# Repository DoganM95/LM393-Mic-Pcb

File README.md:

# LM393-Mic-Pcb
LM393 based microphone module for arduinos. This wil become a part of another bigger project and serves as a copyable module for it. PCB prototype is for testing the circuit and seeing if it catches fire or not.

## Visual Overview
<table>
  <tr>
    <td>
      
    </td>
    <td>
      
    </td>
    <!--
    <td>
      
    </td>
    <td>
      
    </td>
    -->
  </tr>
</table>

## Key Features

- 22.12mm height x 12.7mm width x 1.6mm thickness 
- Adjustable mic sensitivity
- Choosable led colors (short the corresponding jumper)
  - Power Led: JP1:Red, JP2:Green, JP3:Blue,
  - Output Led: JP4:Red, JP5:Green, JP5:Blue

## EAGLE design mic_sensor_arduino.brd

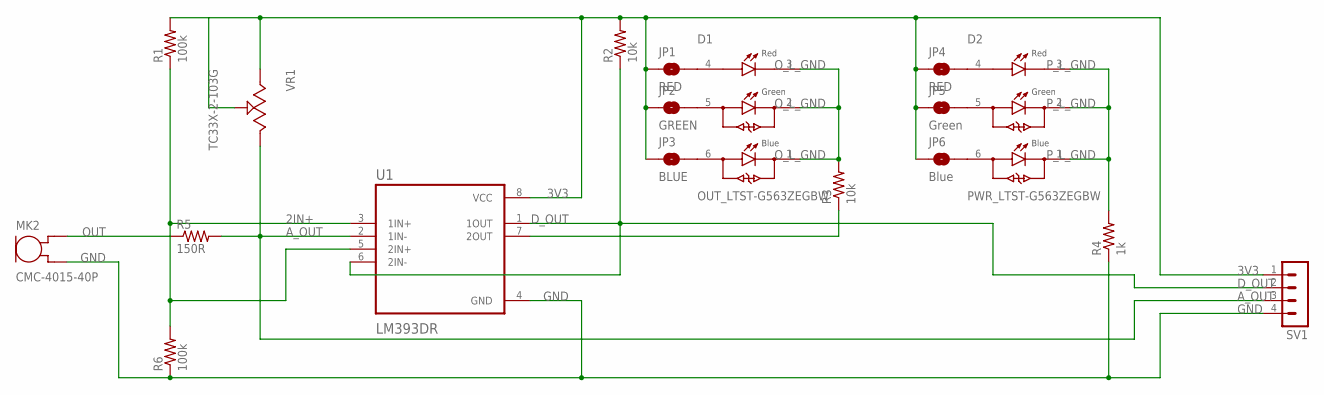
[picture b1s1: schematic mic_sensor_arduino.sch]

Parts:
D1: OUT_LTST-G563ZEGBW; LED_LTST-G563ZEGBW
D2: PWR_LTST-G563ZEGBW; LED_LTST-G563ZEGBW
JP1, JP4: RED; SMT-JUMPER_2_NO_SILK
JP2: GREEN; SMT-JUMPER_2_NO_SILK
JP3: BLUE; SMT-JUMPER_2_NO_SILK
JP5: Green; SMT-JUMPER_2_NO_SILK
JP6: Blue; SMT-JUMPER_2_NO_SILK
MK2: CMC-4015-40P; MIC_CMC-4015-40P
R1, R6: 100k; R0603
R2, R3: 10k; R0603
R4: 1k; R0603
R5: 150R; R0603
SV1: MA04-1
U1: LM393DR; SOIC127P599X175-8N
VR1: TC33X-2-103G; TRIMMER_TC33X-2-103G

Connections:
2IN+: R1.1, R6.2, U1.3 (1IN+), U1.5 (2IN+)
2OUT: R3.1, U1.7 (2OUT)
3V3: JP1.1, JP2.1, JP3.1, JP4.1, JP5.1, JP6.1, R1.2, R2.2, SV1.1, U1.8 (VCC), VR1.1 (CCW), VR1.2 (WIPER)
A_OUT: R5.2, SV1.3, U1.2 (1IN-), VR1.3 (CW)
D_OUT: R2.1, SV1.2, U1.1 (1OUT), U1.6 (2IN-)
GND: MK2.M (GND), R4.1, R6.1, SV1.4, U1.4 (GND)
unnamed: D1.4, JP1.2
unnamed: D1.5, JP2.2
unnamed: D1.6, JP3.2
unnamed: D2.4, JP4.2
unnamed: D2.5, JP5.2
unnamed: D2.6, JP6.2
OUT: MK2.P (OUT), R5.1
O_L_GND: D1.1, D1.2, D1.3, R3.2
P_L_GND: D2.1, D2.2, D2.3, R4.2

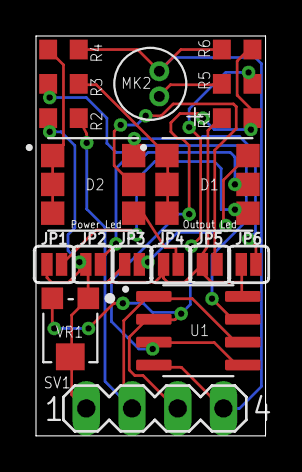
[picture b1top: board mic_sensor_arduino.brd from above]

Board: 2 copper layers, 12.8 x 22.2 mm, 18 parts (0 on the bottom side), 15 nets.

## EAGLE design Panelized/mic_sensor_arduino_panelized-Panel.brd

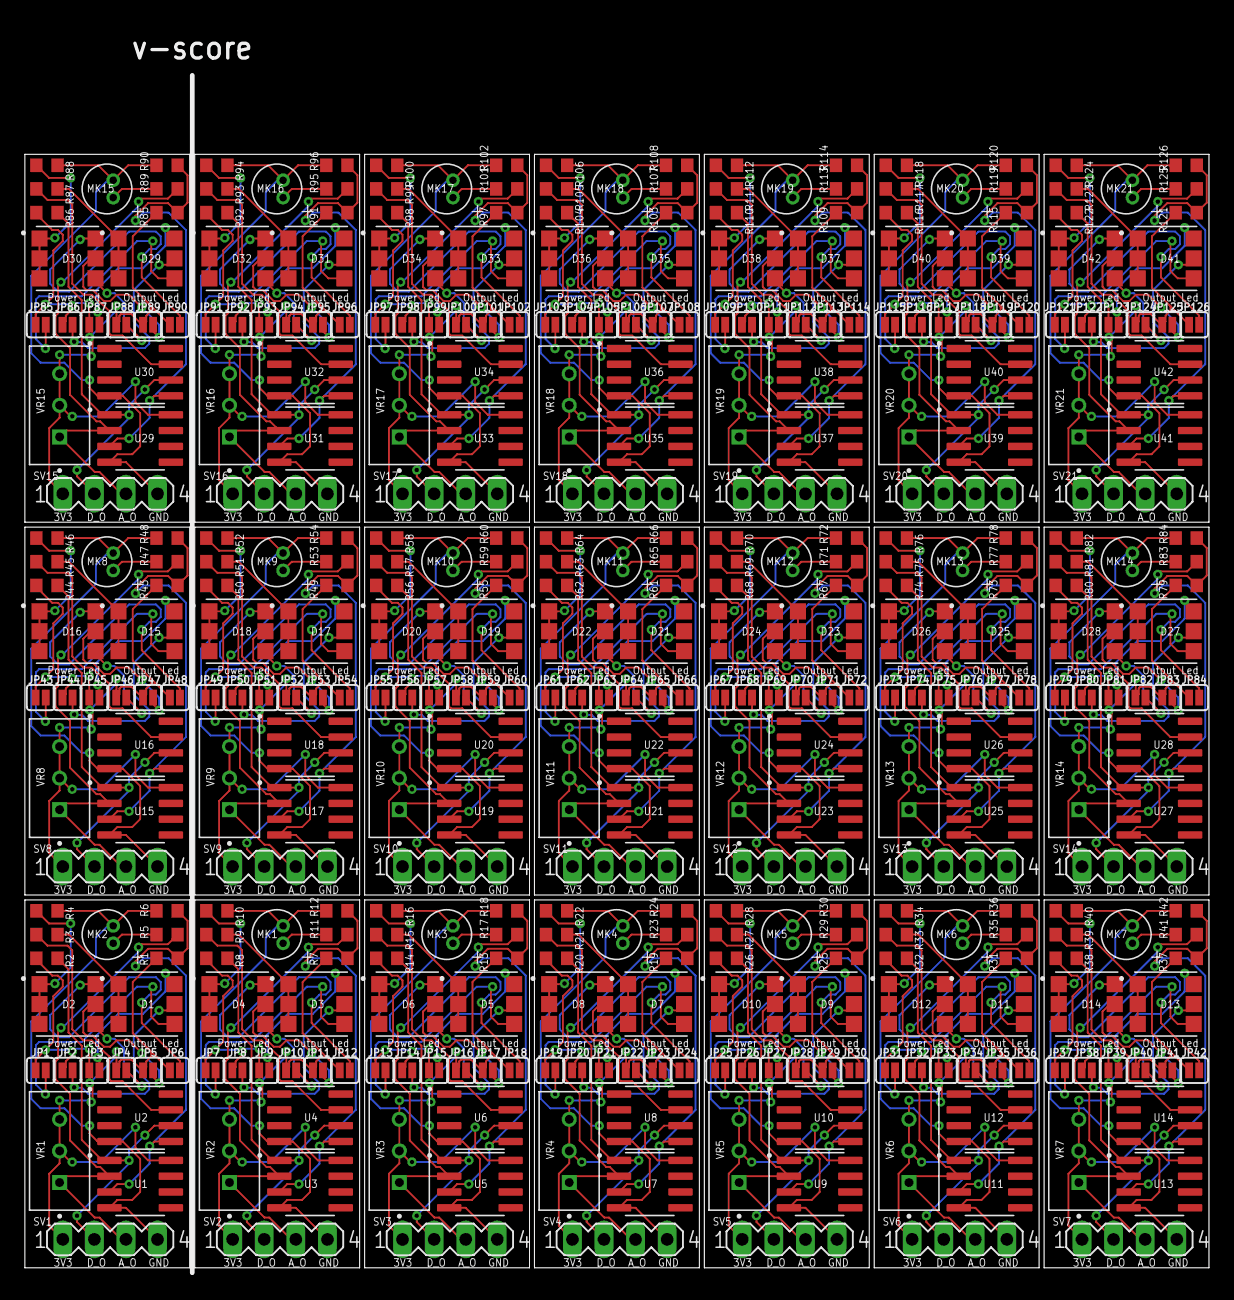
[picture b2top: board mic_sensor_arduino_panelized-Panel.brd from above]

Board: 2 copper layers, 94.8 x 100.2 mm, 399 parts (0 on the bottom side), 315 nets.

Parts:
D1, D3, D5, D7, D9, D11, D13, D15, D17, D19, D21, D23, D25, D27, D29, D31, D33, D35, D37, D39, D41: OUT_LTST-G563ZEGBW; LED_LTST-G563ZEGBW
D2, D4, D6, D8, D10, D12, D14, D16, D18, D20, D22, D24, D26, D28, D30, D32, D34, D36, D38, D40, D42: PWR_LTST-G563ZEGBW; LED_LTST-G563ZEGBW
JP1, JP4, JP7, JP10, JP13, JP16, JP19, JP22, JP25, JP28, JP31, JP34, JP37, JP40, JP43, JP46, JP49, JP52, JP55, JP58, JP61, JP64, JP67, JP70, JP73, JP76, JP79, JP82, JP85, JP88, JP91, JP94, JP97, JP100, JP103, JP106, JP109, JP112, JP115, JP118, JP121, JP124: RED; SMT-JUMPER_2_NO_SILK
JP2, JP8, JP14, JP20, JP26, JP32, JP38, JP44, JP50, JP56, JP62, JP68, JP74, JP80, JP86, JP92, JP98, JP104, JP110, JP116, JP122: GREEN; SMT-JUMPER_2_NO_SILK
JP3, JP9, JP15, JP21, JP27, JP33, JP39, JP45, JP51, JP57, JP63, JP69, JP75, JP81, JP87, JP93, JP99, JP105, JP111, JP117, JP123: BLUE; SMT-JUMPER_2_NO_SILK
JP5, JP11, JP17, JP23, JP29, JP35, JP41, JP47, JP53, JP59, JP65, JP71, JP77, JP83, JP89, JP95, JP101, JP107, JP113, JP119, JP125: Green; SMT-JUMPER_2_NO_SILK
JP6, JP12, JP18, JP24, JP30, JP36, JP42, JP48, JP54, JP60, JP66, JP72, JP78, JP84, JP90, JP96, JP102, JP108, JP114, JP120, JP126: Blue; SMT-JUMPER_2_NO_SILK
MK1, MK2, MK3, MK4, MK5, MK6, MK7, MK8, MK9, MK10, MK11, MK12, MK13, MK14, MK15, MK16, MK17, MK18, MK19, MK20, MK21: CMC-4015-40P; MIC_CMC-4015-40P
R1, R6, R7, R12, R13, R18, R19, R24, R25, R30, R31, R36, R37, R42, R43, R48, R49, R54, R55, R60, R61, R66, R67, R72, R73, R78, R79, R84, R85, R90, R91, R96, R97, R102, R103, R108, R109, R114, R115, R120, R121, R126: 100k; R0603
R2, R3, R8, R9, R14, R15, R20, R21, R26, R27, R32, R33, R38, R39, R44, R45, R50, R51, R56, R57, R62, R63, R68, R69, R74, R75, R80, R81, R86, R87, R92, R93, R98, R99, R104, R105, R110, R111, R116, R117, R122, R123: 10k; R0603
R4, R10, R16, R22, R28, R34, R40, R46, R52, R58, R64, R70, R76, R82, R88, R94, R100, R106, R112, R118, R124: 1k; R0603
R5, R11, R17, R23, R29, R35, R41, R47, R53, R59, R65, R71, R77, R83, R89, R95, R101, R107, R113, R119, R125: 150R; R0603
SV1, SV2, SV3, SV4, SV5, SV6, SV7, SV8, SV9, SV10, SV11, SV12, SV13, SV14, SV15, SV16, SV17, SV18, SV19, SV20, SV21: MA04-1
U1, U2, U3, U4, U5, U6, U7, U8, U9, U10, U11, U12, U13, U14, U15, U16, U17, U18, U19, U20, U21, U22, U23, U24, U25, U26, U27, U28, U29, U30, U31, U32, U33, U34, U35, U36, U37, U38, U39, U40, U41, U42: LM393DR; SOIC127P599X175-8N
VR1, VR2, VR3, VR4, VR5, VR6, VR7, VR8, VR9, VR10, VR11, VR12, VR13, VR14, VR15, VR16, VR17, VR18, VR19, VR20, VR21: 3296W-1-103RLF; TRIM_3296W-1-103RLF

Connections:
2IN+: R1.1, R6.2, U1.3, U2.5
2IN+1: R7.1, R12.2, U3.3, U4.5
2IN+2: R13.1, R18.2, U5.3, U6.5
2IN+3: R19.1, R24.2, U7.3, U8.5
2IN+4: R25.1, R30.2, U9.3, U10.5
2IN+5: R31.1, R36.2, U11.3, U12.5
2IN+6: R37.1, R42.2, U13.3, U14.5
2IN+7: R43.1, R48.2, U15.3, U16.5
2IN+8: R49.1, R54.2, U17.3, U18.5
2IN+9: R55.1, R60.2, U19.3, U20.5
2IN+10: R61.1, R66.2, U21.3, U22.5
2IN+11: R67.1, R72.2, U23.3, U24.5
2IN+12: R73.1, R78.2, U25.3, U26.5
2IN+13: R79.1, R84.2, U27.3, U28.5
2IN+14: R85.1, R90.2, U29.3, U30.5
2IN+15: R91.1, R96.2, U31.3, U32.5
2IN+16: R97.1, R102.2, U33.3, U34.5
2IN+17: R103.1, R108.2, U35.3, U36.5
2IN+18: R109.1, R114.2, U37.3, U38.5
2IN+19: R115.1, R120.2, U39.3, U40.5
2IN+20: R121.1, R126.2, U41.3, U42.5
2OUT: R3.1, U2.7
2OUT1: R9.1, U4.7
2OUT2: R15.1, U6.7
2OUT3: R21.1, U8.7
2OUT4: R27.1, U10.7
2OUT5: R33.1, U12.7
2OUT6: R39.1, U14.7
2OUT7: R45.1, U16.7
2OUT8: R51.1, U18.7
2OUT9: R57.1, U20.7
2OUT10: R63.1, U22.7
2OUT11: R69.1, U24.7
2OUT12: R75.1, U26.7
2OUT13: R81.1, U28.7
2OUT14: R87.1, U30.7
2OUT15: R93.1, U32.7
2OUT16: R99.1, U34.7
2OUT17: R105.1, U36.7
2OUT18: R111.1, U38.7
2OUT19: R117.1, U40.7
2OUT20: R123.1, U42.7
3V1: JP7.1, JP8.1, JP9.1, JP10.1, JP11.1, JP12.1, R7.2, R8.2, SV2.1, U3.8, VR2.2, VR2.3
3V2: JP13.1, JP14.1, JP15.1, JP16.1, JP17.1, JP18.1, R13.2, R14.2, SV3.1, U5.8, VR3.2, VR3.3
3V3: JP1.1, JP2.1, JP3.1, JP4.1, JP5.1, JP6.1, R1.2, R2.2, SV1.1, U1.8, VR1.2, VR1.3
3V4: JP19.1, JP20.1, JP21.1, JP22.1, JP23.1, JP24.1, R19.2, R20.2, SV4.1, U7.8, VR4.2, VR4.3
3V5: JP25.1, JP26.1, JP27.1, JP28.1, JP29.1, JP30.1, R25.2, R26.2, SV5.1, U9.8, VR5.2, VR5.3
3V6: JP31.1, JP32.1, JP33.1, JP34.1, JP35.1, JP36.1, R31.2, R32.2, SV6.1, U11.8, VR6.2, VR6.3
3V7: JP37.1, JP38.1, JP39.1, JP40.1, JP41.1, JP42.1, R37.2, R38.2, SV7.1, U13.8, VR7.2, VR7.3
3V8: JP43.1, JP44.1, JP45.1, JP46.1, JP47.1, JP48.1, R43.2, R44.2, SV8.1, U15.8, VR8.2, VR8.3
3V9: JP49.1, JP50.1, JP51.1, JP52.1, JP53.1, JP54.1, R49.2, R50.2, SV9.1, U17.8, VR9.2, VR9.3
3V10: JP55.1, JP56.1, JP57.1, JP58.1, JP59.1, JP60.1, R55.2, R56.2, SV10.1, U19.8, VR10.2, VR10.3
3V11: JP61.1, JP62.1, JP63.1, JP64.1, JP65.1, JP66.1, R61.2, R62.2, SV11.1, U21.8, VR11.2, VR11.3
3V12: JP67.1, JP68.1, JP69.1, JP70.1, JP71.1, JP72.1, R67.2, R68.2, SV12.1, U23.8, VR12.2, VR12.3
3V13: JP73.1, JP74.1, JP75.1, JP76.1, JP77.1, JP78.1, R73.2, R74.2, SV13.1, U25.8, VR13.2, VR13.3
3V14: JP79.1, JP80.1, JP81.1, JP82.1, JP83.1, JP84.1, R79.2, R80.2, SV14.1, U27.8, VR14.2, VR14.3
3V15: JP85.1, JP86.1, JP87.1, JP88.1, JP89.1, JP90.1, R85.2, R86.2, SV15.1, U29.8, VR15.2, VR15.3
3V16: JP91.1, JP92.1, JP93.1, JP94.1, JP95.1, JP96.1, R91.2, R92.2, SV16.1, U31.8, VR16.2, VR16.3
3V17: JP97.1, JP98.1, JP99.1, JP100.1, JP101.1, JP102.1, R97.2, R98.2, SV17.1, U33.8, VR17.2, VR17.3
3V18: JP103.1, JP104.1, JP105.1, JP106.1, JP107.1, JP108.1, R103.2, R104.2, SV18.1, U35.8, VR18.2, VR18.3
3V19: JP109.1, JP110.1, JP111.1, JP112.1, JP113.1, JP114.1, R109.2, R110.2, SV19.1, U37.8, VR19.2, VR19.3
3V20: JP115.1, JP116.1, JP117.1, JP118.1, JP119.1, JP120.1, R115.2, R116.2, SV20.1, U39.8, VR20.2, VR20.3
3V21: JP121.1, JP122.1, JP123.1, JP124.1, JP125.1, JP126.1, R121.2, R122.2, SV21.1, U41.8, VR21.2, VR21.3
A_OUT: R5.2, SV1.3, U1.2, VR1.1
A_OUT1: R11.2, SV2.3, U3.2, VR2.1
A_OUT2: R17.2, SV3.3, U5.2, VR3.1
A_OUT3: R23.2, SV4.3, U7.2, VR4.1
A_OUT4: R29.2, SV5.3, U9.2, VR5.1
A_OUT5: R35.2, SV6.3, U11.2, VR6.1
A_OUT6: R41.2, SV7.3, U13.2, VR7.1
A_OUT7: R47.2, SV8.3, U15.2, VR8.1
A_OUT8: R53.2, SV9.3, U17.2, VR9.1
A_OUT9: R59.2, SV10.3, U19.2, VR10.1
A_OUT10: R65.2, SV11.3, U21.2, VR11.1
A_OUT11: R71.2, SV12.3, U23.2, VR12.1
A_OUT12: R77.2, SV13.3, U25.2, VR13.1
A_OUT13: R83.2, SV14.3, U27.2, VR14.1
A_OUT14: R89.2, SV15.3, U29.2, VR15.1
A_OUT15: R95.2, SV16.3, U31.2, VR16.1
A_OUT16: R101.2, SV17.3, U33.2, VR17.1
A_OUT17: R107.2, SV18.3, U35.2, VR18.1
A_OUT18: R113.2, SV19.3, U37.2, VR19.1
A_OUT19: R119.2, SV20.3, U39.2, VR20.1
A_OUT20: R125.2, SV21.3, U41.2, VR21.1
D_OUT: R2.1, SV1.2, U1.1, U2.6
D_OUT1: R8.1, SV2.2, U3.1, U4.6
D_OUT2: R14.1, SV3.2, U5.1, U6.6
D_OUT3: R20.1, SV4.2, U7.1, U8.6
D_OUT4: R26.1, SV5.2, U9.1, U10.6
D_OUT5: R32.1, SV6.2, U11.1, U12.6
D_OUT6: R38.1, SV7.2, U13.1, U14.6
D_OUT7: R44.1, SV8.2, U15.1, U16.6
D_OUT8: R50.1, SV9.2, U17.1, U18.6
D_OUT9: R56.1, SV10.2, U19.1, U20.6
D_OUT10: R62.1, SV11.2, U21.1, U22.6
D_OUT11: R68.1, SV12.2, U23.1, U24.6
D_OUT12: R74.1, SV13.2, U25.1, U26.6
D_OUT13: R80.1, SV14.2, U27.1, U28.6
D_OUT14: R86.1, SV15.2, U29.1, U30.6
D_OUT15: R92.1, SV16.2, U31.1, U32.6
D_OUT16: R98.1, SV17.2, U33.1, U34.6
D_OUT17: R104.1, SV18.2, U35.1, U36.6
D_OUT18: R110.1, SV19.2, U37.1, U38.6
D_OUT19: R116.1, SV20.2, U39.1, U40.6
D_OUT20: R122.1, SV21.2, U41.1, U42.6
GND: MK2.M, R4.1, R6.1, SV1.4, U1.4, U2.4
GND1: MK1.M, R10.1, R12.1, SV2.4, U3.4, U4.4
GND2: MK3.M, R16.1, R18.1, SV3.4, U5.4, U6.4
GND3: MK4.M, R22.1, R24.1, SV4.4, U7.4, U8.4
GND4: MK5.M, R28.1, R30.1, SV5.4, U9.4, U10.4
GND5: MK6.M, R34.1, R36.1, SV6.4, U11.4, U12.4
GND6: MK7.M, R40.1, R42.1, SV7.4, U13.4, U14.4
GND7: MK8.M, R46.1, R48.1, SV8.4, U15.4, U16.4
GND8: MK9.M, R52.1, R54.1, SV9.4, U17.4, U18.4
GND9: MK10.M, R58.1, R60.1, SV10.4, U19.4, U20.4
GND10: MK11.M, R64.1, R66.1, SV11.4, U21.4, U22.4
GND11: MK12.M, R70.1, R72.1, SV12.4, U23.4, U24.4
GND12: MK13.M, R76.1, R78.1, SV13.4, U25.4, U26.4
GND13: MK14.M, R82.1, R84.1, SV14.4, U27.4, U28.4
GND14: MK15.M, R88.1, R90.1, SV15.4, U29.4, U30.4
GND15: MK16.M, R94.1, R96.1, SV16.4, U31.4, U32.4
GND16: MK17.M, R100.1, R102.1, SV17.4, U33.4, U34.4
GND17: MK18.M, R106.1, R108.1, SV18.4, U35.4, U36.4
GND18: MK19.M, R112.1, R114.1, SV19.4, U37.4, U38.4
GND19: MK20.M, R118.1, R120.1, SV20.4, U39.4, U40.4
GND20: MK21.M, R124.1, R126.1, SV21.4, U41.4, U42.4
unnamed: D1.4, JP1.2
unnamed: D1.5, JP2.2
unnamed: D3.4, JP7.2
unnamed: D3.5, JP8.2
unnamed: D1.6, JP3.2
unnamed: D2.4, JP4.2
unnamed: D2.5, JP5.2
unnamed: D2.6, JP6.2
unnamed: D3.6, JP9.2
unnamed: D4.4, JP10.2
unnamed: D4.5, JP11.2
unnamed: D4.6, JP12.2
unnamed: D5.4, JP13.2
unnamed: D5.5, JP14.2
unnamed: D5.6, JP15.2
unnamed: D6.4, JP16.2
unnamed: D6.5, JP17.2
unnamed: D6.6, JP18.2
unnamed: D7.4, JP19.2
unnamed: D7.5, JP20.2
unnamed: D7.6, JP21.2
unnamed: D8.4, JP22.2
unnamed: D8.5, JP23.2
unnamed: D8.6, JP24.2
unnamed: D9.4, JP25.2
unnamed: D9.5, JP26.2
unnamed: D9.6, JP27.2
unnamed: D10.4, JP28.2
unnamed: D10.5, JP29.2
unnamed: D10.6, JP30.2
unnamed: D11.4, JP31.2
unnamed: D11.5, JP32.2
unnamed: D11.6, JP33.2
unnamed: D12.4, JP34.2
unnamed: D12.5, JP35.2
unnamed: D12.6, JP36.2
unnamed: D13.4, JP37.2
unnamed: D13.5, JP38.2
unnamed: D13.6, JP39.2
unnamed: D14.4, JP40.2
unnamed: D14.5, JP41.2
unnamed: D14.6, JP42.2
unnamed: D15.4, JP43.2
unnamed: D15.5, JP44.2
unnamed: D15.6, JP45.2
unnamed: D16.4, JP46.2
unnamed: D16.5, JP47.2
unnamed: D16.6, JP48.2
unnamed: D17.4, JP49.2
unnamed: D17.5, JP50.2
unnamed: D17.6, JP51.2
unnamed: D18.4, JP52.2
unnamed: D18.5, JP53.2
unnamed: D18.6, JP54.2
unnamed: D19.4, JP55.2
unnamed: D19.5, JP56.2
unnamed: D19.6, JP57.2
unnamed: D20.4, JP58.2
unnamed: D20.5, JP59.2
unnamed: D20.6, JP60.2
unnamed: D21.4, JP61.2
unnamed: D21.5, JP62.2
unnamed: D21.6, JP63.2
unnamed: D22.4, JP64.2
unnamed: D22.5, JP65.2
unnamed: D22.6, JP66.2
unnamed: D23.4, JP67.2
unnamed: D23.5, JP68.2
unnamed: D23.6, JP69.2
unnamed: D24.4, JP70.2
unnamed: D24.5, JP71.2
unnamed: D24.6, JP72.2
unnamed: D25.4, JP73.2
unnamed: D25.5, JP74.2
unnamed: D25.6, JP75.2
unnamed: D26.4, JP76.2
unnamed: D26.5, JP77.2
unnamed: D26.6, JP78.2
unnamed: D27.4, JP79.2
unnamed: D27.5, JP80.2
unnamed: D27.6, JP81.2
unnamed: D28.4, JP82.2
unnamed: D28.5, JP83.2
unnamed: D28.6, JP84.2
unnamed: D29.4, JP85.2
unnamed: D29.5, JP86.2
unnamed: D29.6, JP87.2
unnamed: D30.4, JP88.2
unnamed: D30.5, JP89.2
unnamed: D30.6, JP90.2
unnamed: D31.4, JP91.2
unnamed: D31.5, JP92.2
unnamed: D31.6, JP93.2
unnamed: D32.4, JP94.2
unnamed: D32.5, JP95.2
unnamed: D32.6, JP96.2
unnamed: D33.4, JP97.2
unnamed: D33.5, JP98.2
unnamed: D33.6, JP99.2
unnamed: D34.4, JP100.2
unnamed: D34.5, JP101.2
unnamed: D34.6, JP102.2
unnamed: D35.4, JP103.2
unnamed: D35.5, JP104.2
unnamed: D35.6, JP105.2
unnamed: D36.4, JP106.2
unnamed: D36.5, JP107.2
unnamed: D36.6, JP108.2
unnamed: D37.4, JP109.2
unnamed: D37.5, JP110.2
unnamed: D37.6, JP111.2
unnamed: D38.4, JP112.2
unnamed: D38.5, JP113.2
unnamed: D38.6, JP114.2
unnamed: D39.4, JP115.2
unnamed: D39.5, JP116.2
unnamed: D39.6, JP117.2
unnamed: D40.4, JP118.2
unnamed: D40.5, JP119.2
unnamed: D40.6, JP120.2
unnamed: D41.4, JP121.2
unnamed: D41.5, JP122.2
unnamed: D41.6, JP123.2
unnamed: D42.4, JP124.2
unnamed: D42.5, JP125.2
unnamed: D42.6, JP126.2
OUT: MK2.P, R5.1
OUT1: MK1.P, R11.1
OUT2: MK3.P, R17.1
OUT3: MK4.P, R23.1
OUT4: MK5.P, R29.1
OUT5: MK6.P, R35.1
OUT6: MK7.P, R41.1
OUT7: MK8.P, R47.1
OUT8: MK9.P, R53.1
OUT9: MK10.P, R59.1
OUT10: MK11.P, R65.1
OUT11: MK12.P, R71.1
OUT12: MK13.P, R77.1
OUT13: MK14.P, R83.1
OUT14: MK15.P, R89.1
OUT15: MK16.P, R95.1
OUT16: MK17.P, R101.1
OUT17: MK18.P, R107.1
OUT18: MK19.P, R113.1
OUT19: MK20.P, R119.1
OUT20: MK21.P, R125.1
O_L_GND: D1.1, D1.2, D1.3, R3.2
O_L_GND1: D3.1, D3.2, D3.3, R9.2
O_L_GND2: D5.1, D5.2, D5.3, R15.2
O_L_GND3: D7.1, D7.2, D7.3, R21.2
O_L_GND4: D9.1, D9.2, D9.3, R27.2
O_L_GND5: D11.1, D11.2, D11.3, R33.2
O_L_GND6: D13.1, D13.2, D13.3, R39.2
O_L_GND7: D15.1, D15.2, D15.3, R45.2
O_L_GND8: D17.1, D17.2, D17.3, R51.2
O_L_GND9: D19.1, D19.2, D19.3, R57.2
O_L_GND10: D21.1, D21.2, D21.3, R63.2
O_L_GND11: D23.1, D23.2, D23.3, R69.2
O_L_GND12: D25.1, D25.2, D25.3, R75.2
O_L_GND13: D27.1, D27.2, D27.3, R81.2
O_L_GND14: D29.1, D29.2, D29.3, R87.2
O_L_GND15: D31.1, D31.2, D31.3, R93.2
O_L_GND16: D33.1, D33.2, D33.3, R99.2
O_L_GND17: D35.1, D35.2, D35.3, R105.2
O_L_GND18: D37.1, D37.2, D37.3, R111.2
O_L_GND19: D39.1, D39.2, D39.3, R117.2
O_L_GND20: D41.1, D41.2, D41.3, R123.2
P_L_GND: D2.1, D2.2, D2.3, R4.2
P_L_GND1: D4.1, D4.2, D4.3, R10.2
P_L_GND2: D6.1, D6.2, D6.3, R16.2
P_L_GND3: D8.1, D8.2, D8.3, R22.2
P_L_GND4: D10.1, D10.2, D10.3, R28.2
P_L_GND5: D12.1, D12.2, D12.3, R34.2
P_L_GND6: D14.1, D14.2, D14.3, R40.2
P_L_GND7: D16.1, D16.2, D16.3, R46.2
P_L_GND8: D18.1, D18.2, D18.3, R52.2
P_L_GND9: D20.1, D20.2, D20.3, R58.2
P_L_GND10: D22.1, D22.2, D22.3, R64.2
P_L_GND11: D24.1, D24.2, D24.3, R70.2
P_L_GND12: D26.1, D26.2, D26.3, R76.2
P_L_GND13: D28.1, D28.2, D28.3, R82.2
P_L_GND14: D30.1, D30.2, D30.3, R88.2
P_L_GND15: D32.1, D32.2, D32.3, R94.2
P_L_GND16: D34.1, D34.2, D34.3, R100.2
P_L_GND17: D36.1, D36.2, D36.3, R106.2
P_L_GND18: D38.1, D38.2, D38.3, R112.2
P_L_GND19: D40.1, D40.2, D40.3, R118.2
P_L_GND20: D42.1, D42.2, D42.3, R124.2

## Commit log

2023-11-18 init prototype
2023-11-18 create release
2023-11-18 experimental penalization
2023-11-18 reorganize files
2024-08-15 update preview
2024-08-15 update resources

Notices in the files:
parts and their libraries:
SparkFun-Jumpers: Licensing: Creative Commons ShareAlike 4.0 International - https://creativecommons.org/licenses/by-sa/4.0
